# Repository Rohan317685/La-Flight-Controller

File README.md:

I present you fira:
A flight controller!
I have made a accurate ish render of the frame we have spent somewhat weeks its just we were trying to make sure it was affordable and have some lists for kits this could be in!
It has 4 s12302 Mosfets and a esp32-s3-wroom-1 controller and can be controlled entirely via WIFI!

I attached a render of what it can be used for :) Its meant for simple tiny drones!

That is the schematic + pcb!
Credits to:

@Rohan for creating the render, schematic and repo
@traffic person for routing the entire pcb and helping with technical issues!

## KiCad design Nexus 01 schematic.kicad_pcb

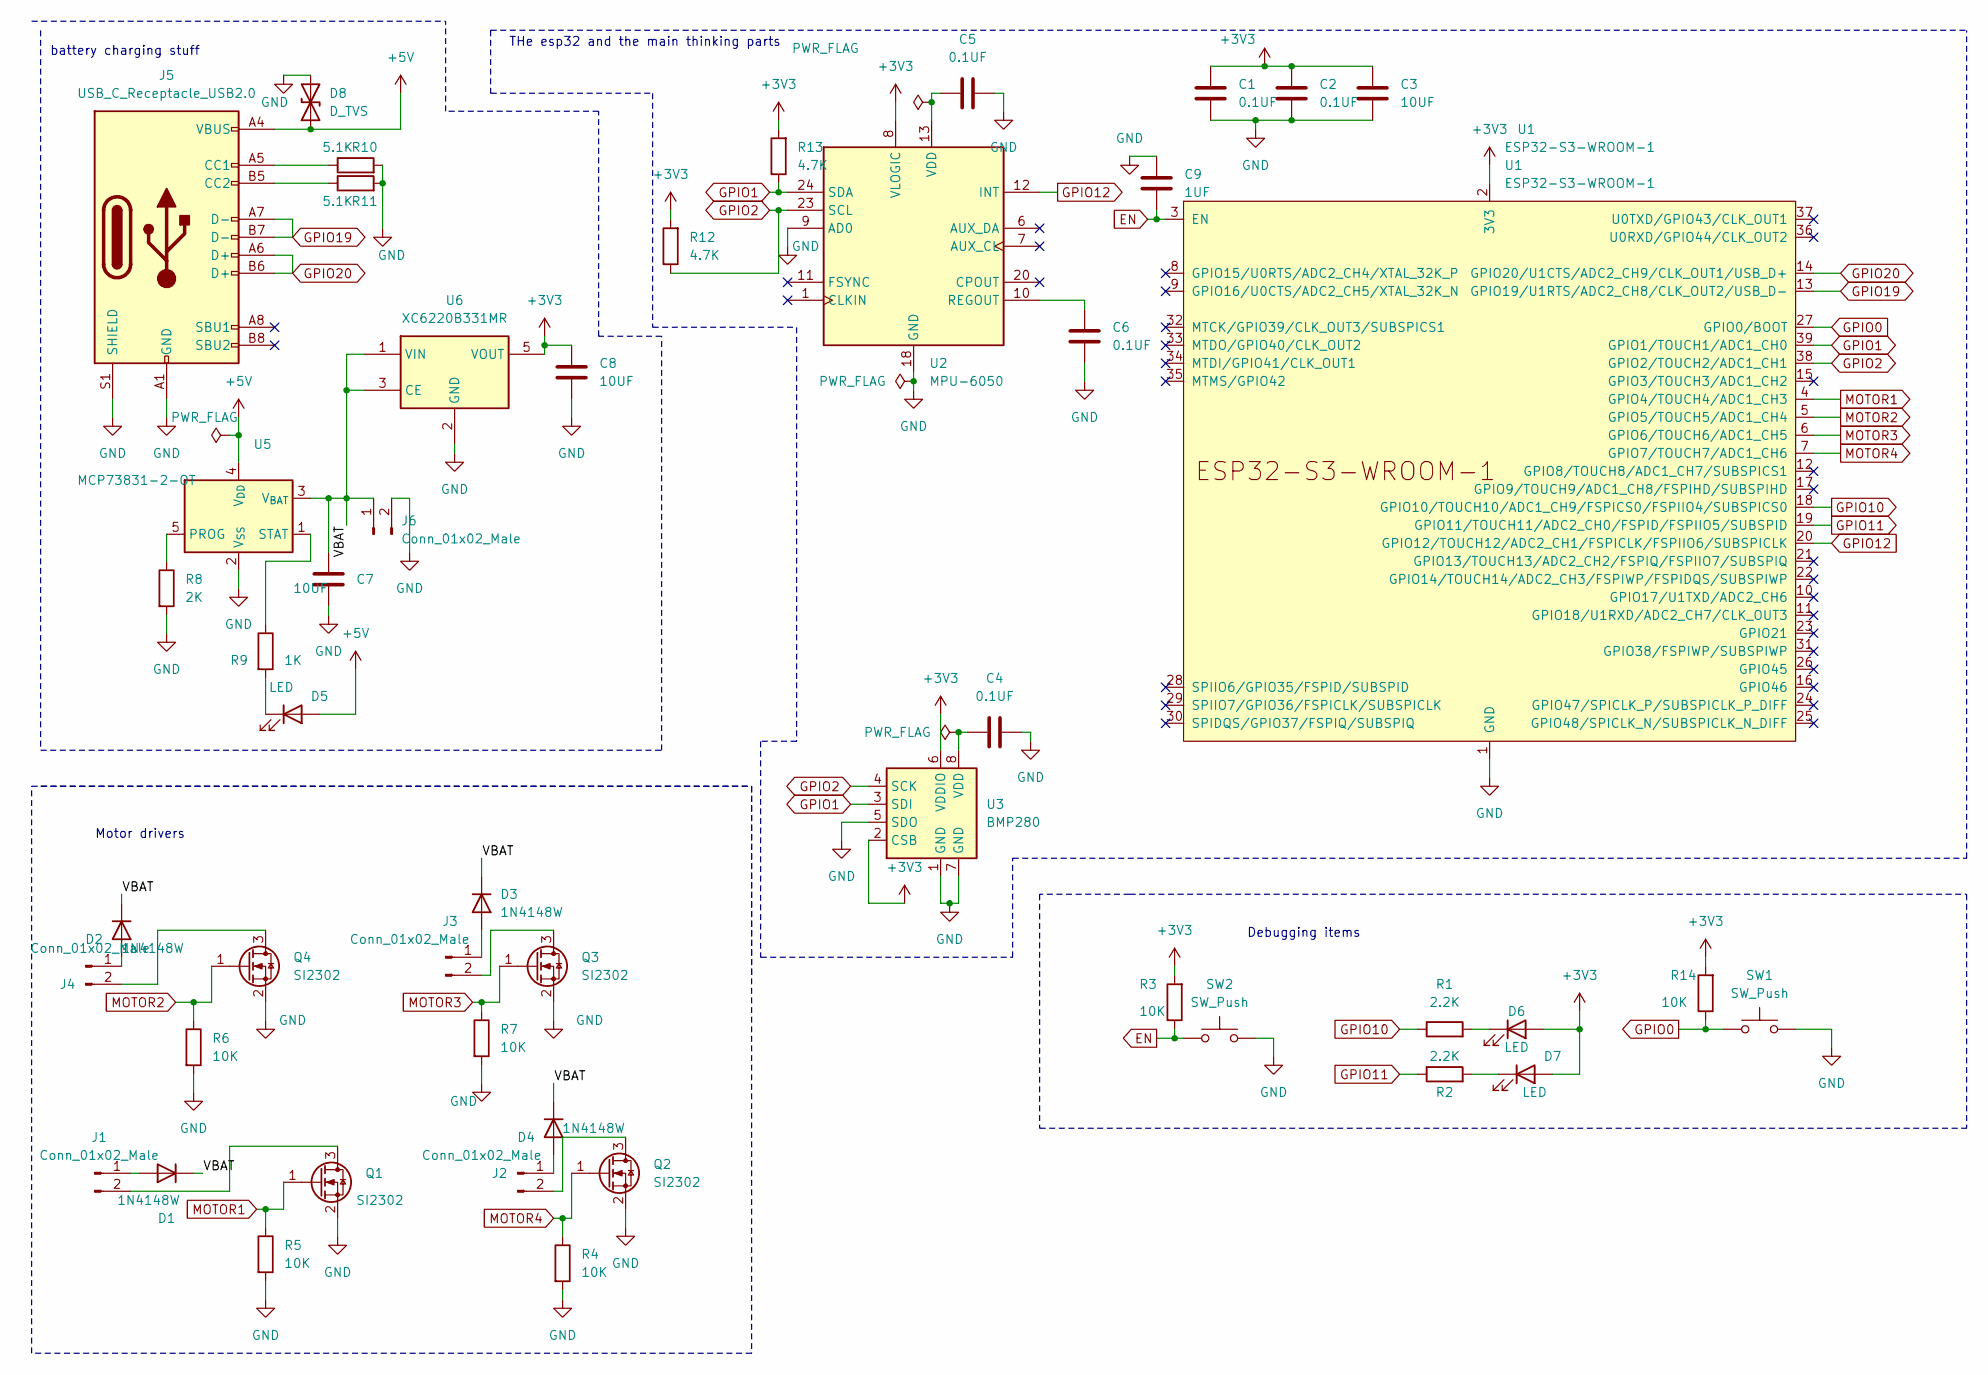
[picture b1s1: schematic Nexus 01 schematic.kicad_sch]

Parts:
C1, C2, C4, C5, C6: 0.1UF; C_0603_1608Metric
C3, C7, C8: 10UF; C_0805_2012Metric
C9: 1UF; C_0603_1608Metric
D1, D2, D3, D4: 1N4148W; D_SOD-123
D5, D6, D7: LED; LED_0603_1608Metric
D8: D_TVS; D_SOD-323
J1, J2, J3, J4, J6: Conn_01x02_Male; PinHeader_1x02_P1.00mm_Vertical
J5: USB_C_Receptacle_USB2.0; USB_C_Receptacle_HRO_TYPE-C-31-M-12
Q1, Q2, Q3, Q4: SI2302; SOT-23
R1, R2: 2.2K; R_0603_1608Metric
R3, R4, R5, R6, R7, R14: 10K; R_0603_1608Metric
R8: 2K; R_0603_1608Metric
R9: 1K; R_0603_1608Metric
R10, R11: 5.1K; R_0603_1608Metric
R12, R13: 4.7K; R_0603_1608Metric
SW1, SW2: SW_Push; SW_Push_1TS009xxxx-xxxx-xxxx_6x6x5mm
U1: ESP32-S3-WROOM-1
U2: MPU-6050; InvenSense_QFN-24_4x4mm_P0.5mm
U3: BMP280; Bosch_LGA-8_2x2.5mm_P0.65mm_ClockwisePinNumbering
U5: MCP73831-2-OT; SOT-23-5
U6: XC6220B331MR; SOT-23-5

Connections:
+3V3: C1.1, C2.1, C3.1, C8.1, D6.2 (A), D7.2 (A), R3.2, R12.2, R13.2, R14.2, U1.2 (3V3), U2.8 (VLOGIC), U3.2 (CSB), U3.6 (VDDIO), U6.5 (VOUT)
+5V: D5.2 (A), D8.1 (A1), J5.A4 (VBUS), J5.A9 (VBUS), J5.B4 (VBUS), J5.B9 (VBUS), U5.4 (V_{DD})
/VBAT: C7.1, D1.1 (K), D2.1 (K), D3.1 (K), D4.1 (K), J6.1, U5.3 (V_{BAT}), U6.1 (VIN), U6.3 (CE)
EN: C9.2, R3.1, SW2.1, U1.3 (EN)
GND: C1.2, C2.2, C3.2, C4.1, C5.2, C6.2, C7.2, C8.2, C9.1, D8.2 (A2), J5.A1 (GND), J5.A12 (GND), J5.B1 (GND), J5.B12 (GND), J5.S1 (SHIELD), J6.2, Q1.2 (S), Q2.2 (S), Q3.2 (S), Q4.2 (S), R4.2, R5.2, R6.2, R7.2, R8.2, R10.2, R11.2, SW1.2, SW2.2, U1.1 (GND), U1.40 (GND), U1.41 (GND), U2.9 (AD0), U2.18 (GND), U3.1 (GND), U3.5 (SDO), U3.7 (GND), U5.2 (V_{SS}), U6.2 (GND)
GPIO0: R14.1, SW1.1, U1.27 (GPIO0/BOOT)
GPIO1: R13.1, U1.39 (GPIO1/TOUCH1/ADC1_CH0), U2.24 (SDA), U3.3 (SDI)
GPIO2: R12.1, U1.38 (GPIO2/TOUCH2/ADC1_CH1), U2.23 (SCL), U3.4 (SCK)
GPIO10: R1.1, U1.18 (GPIO10/TOUCH10/ADC1_CH9/FSPICS0/FSPIIO4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)
GPIO11: R2.1, U1.19 (GPIO11/TOUCH11/ADC2_CH0/FSPID/FSPIIO5/S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)
GPIO12: U1.20 (GPIO12/TOUCH12/ADC2_CH1/FSPICLK/FSPIIO6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), U2.12 (INT)
GPIO19: J5.A7 (D-), J5.B7 (D-), U1.13 (GPIO19/U1RTS/ADC2_CH8/CLK_OUT2/USB_D-)
GPIO20: J5.A6 (D+), J5.B6 (D+), U1.14 (GPIO20/U1CTS/ADC2_CH9/CLK_OUT1/USB_D+)
MOTOR1: Q1.1 (G), R5.1, U1.4 (GPIO4/TOUCH4/ADC1_CH3)
MOTOR2: Q4.1 (G), R6.1, U1.5 (GPIO5/TOUCH5/ADC1_CH4)
MOTOR3: Q3.1 (G), R7.1, U1.6 (GPIO6/TOUCH6/ADC1_CH5)
MOTOR4: Q2.1 (G), R4.1, U1.7 (GPIO7/TOUCH7/ADC1_CH6)
unnamed: D1.2 (A), J1.1
unnamed: D2.2 (A), J4.1
unnamed: D3.2 (A), J3.1
unnamed: D4.2 (A), J2.1
unnamed: D5.1 (K), R9.2
unnamed: D6.1 (K), R1.2
unnamed: D7.1 (K), R2.2
unnamed: J1.2, Q1.3 (D)
unnamed: J2.2, Q2.3 (D)
unnamed: J3.2, Q3.3 (D)
unnamed: J4.2, Q4.3 (D)
unnamed: J5.A5 (CC1), R10.1
unnamed: J5.B5 (CC2), R11.1
unnamed: C6.1, U2.10 (REGOUT)
unnamed: C5.1, U2.13 (VDD)
unnamed: C4.2, U3.8 (VDD)
unnamed: R8.1, U5.5 (PROG)
unnamed: R9.1, U5.1 (STAT)

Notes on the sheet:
THe esp32 and the main thinking parts
Motor drivers
battery charging stuff
Debugging items

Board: 4 copper layers, 48 parts (0 on the bottom side), 35 nets, no tracks yet.

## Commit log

2026-03-01 I organised the flight controllers better
